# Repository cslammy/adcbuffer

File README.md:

# adcbuffer
Op amp buffer with clamp, to protect your MCU's ADC pins

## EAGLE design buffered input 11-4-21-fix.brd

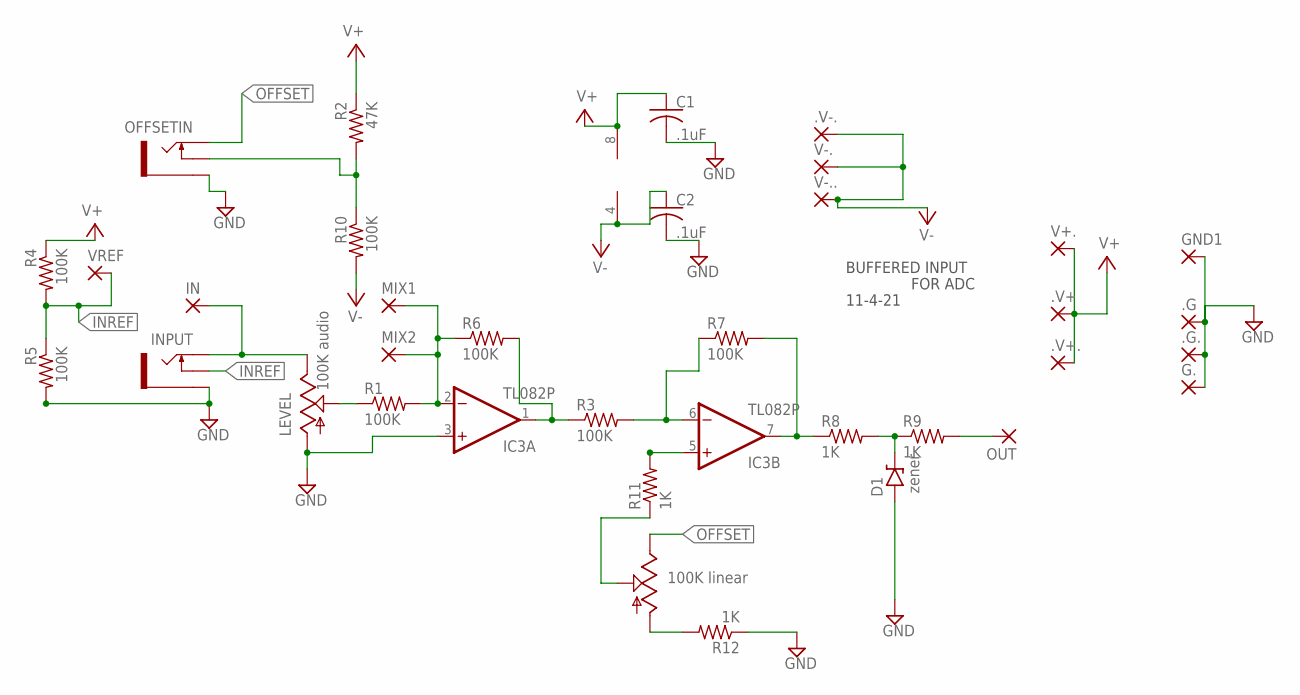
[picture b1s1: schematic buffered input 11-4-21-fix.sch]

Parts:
.G, .G., .V-.: 3,17/1,3
.V+, .V+.: 2,54/1,0
C1, C2: .1uF; C025-025X050
D1: zener; DO41-2
G.: 3,17/1,3
GND1: 3,17/1,3
IC3: TL082P; DIL08
IN: 3,17/1,3
INPUT: THONKICONNNEW; WQP-PJ301M-12_JACK
LEVEL: 100K audio; 9MM_SNAP-IN_POT
MIX1, MIX2: 3,17/1,3
OFFSET: 100K linear; 9MM_SNAP-IN_POT
OFFSETIN: THONKICONNNEW; WQP-PJ301M-12_JACK
OUT: 3,17/1,3
R1, R3, R4, R5, R6, R7, R10: 100K; 0204/7
R2: 47K; 0204/7
R8, R9, R11, R12: 1K; 0204/7
V+.: 2,54/1,0
V-., V-..: 3,17/1,3
VREF: 3,17/1,3

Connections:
CHARREF: OFFSETIN.P$2_SWITCH (SWITCH), R2.2, R10.1
GND: .G.1, .G..1, C1.2, C2.2, D1.A, G..1, GND1.1, IC3.3 (+IN), INPUT.P$3_SLEEVE (SLEEVE), LEVEL.1 (A), OFFSETIN.P$3_SLEEVE (SLEEVE), R5.2, R12.1
INREF: INPUT.P$2_SWITCH (SWITCH), R4.2, R5.1, VREF.1
unnamed: IN.1, INPUT.P$1_TIP (TIP), LEVEL.3 (E)
unnamed: OUT.1, R9.2
unnamed: OFFSET.1 (A), R12.2
unnamed: IC3.5 (+IN), R11.2
unnamed: IC3.6 (-IN), R3.2, R7.1
unnamed: IC3.1 (OUT), R3.1, R6.2
unnamed: IC3.2 (-IN), MIX1.1, MIX2.1, R1.2, R6.1
unnamed: LEVEL.2 (S), R1.1
unnamed: OFFSET.2 (S), R11.1
unnamed: IC3.7 (OUT), R7.2, R8.1
unnamed: D1.C, R8.2, R9.1
OFFSET: OFFSET.3 (E), OFFSETIN.P$1_TIP (TIP)
V+: .V+.1, .V+..1, C1.1, IC3.8 (V+), R2.1, R4.1, V+..1
V-: .V-..1, C2.1, IC3.4 (V-), R10.2, V-..1, V-...1

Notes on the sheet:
BUFFERED INPUT
11-4-21
FOR ADC

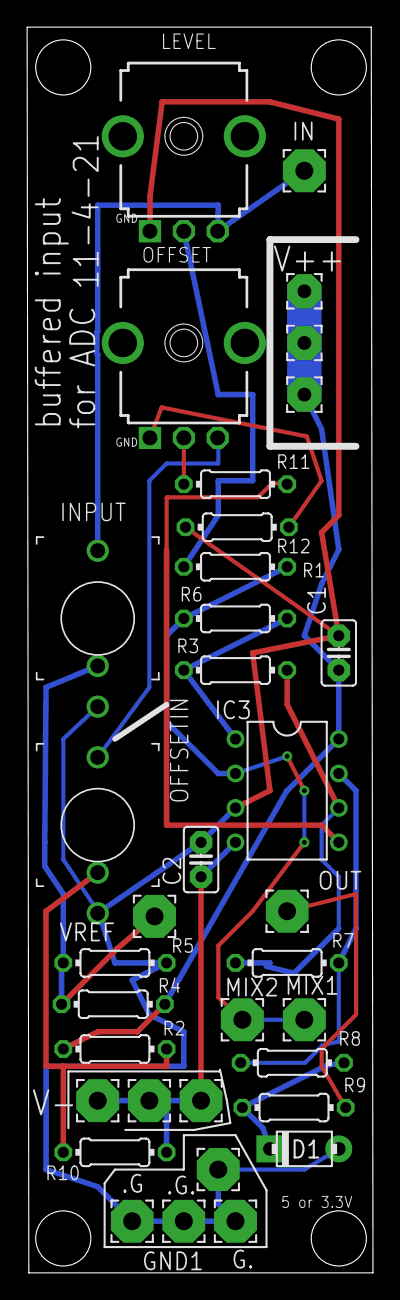
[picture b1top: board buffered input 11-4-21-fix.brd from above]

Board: 2 copper layers, 25.5 x 91.9 mm, 35 parts (0 on the bottom side), 17 nets.

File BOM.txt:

Part     Value       Device           Package            Description                                       DATA_SHEET                                                            
                                                                                                        
C1       .1uF        C-US025-025X050  C025-025X050       CAPACITOR, American symbol                                                                                              
C2       .1uF        C-US025-025X050  C025-025X050       CAPACITOR, American symbol                                                                                              
D1       zener       ZENER.2          DO41-2             5V zener diode                                                                                                                        
                                                                                                        
IC3      TL082P      TL082P           DIL08              OP AMP                                             Data sheet 
                                                                                                        
INPUT                THONKICONNNEW    WQP-PJ301M-12_JACK 3.5mm socket for Eurorack modular synths                                                                                
LEVEL    100K audio  9MM_SNAP-IN_POT_ 9MM_SNAP-IN_POT    9mm vertical snap-in pot, Alpha / Panasonic style                                                                       
                                                                                                      
OFFSET   100K linear 9MM_SNAP-IN_POT_ 9MM_SNAP-IN_POT    9mm vertical snap-in pot, Alpha / Panasonic style                                                                       
OFFSETIN             THONKICONNNEW    WQP-PJ301M-12_JACK 3.5mm socket for Eurorack modular synths                                                                                
                                                                                                        
R1       100K        R-US_0204/7      0204/7             RESISTOR, American symbol                                                                                               
R2       47K         R-US_0204/7      0204/7             RESISTOR, American symbol                                                                                               
R3       100K        R-US_0204/7      0204/7             RESISTOR, American symbol                                                                                               
R4       100K        R-US_0204/7      0204/7             RESISTOR, American symbol                                                                                               
R5       100K        R-US_0204/7      0204/7             RESISTOR, American symbol                                                                                               
R6       100K        R-US_0204/7      0204/7             RESISTOR, American symbol                                                                                               
R7       100K        R-US_0204/7      0204/7             RESISTOR, American symbol                                                                                               
R8       1K          R-US_0204/7      0204/7             RESISTOR, American symbol                                                                                               
R9       1K          R-US_0204/7      0204/7             RESISTOR, American symbol                                                                                               
R10      100K        R-US_0204/7      0204/7             RESISTOR, American symbol                                                                                               
R11      1K          R-US_0204/7      0204/7             RESISTOR, American symbol                                                                                               
R12      1K          R-US_0204/7      0204/7             RESISTOR, American symbol

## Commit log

2022-01-30 Initial upload--gerber, BOM, eagle files, PDFs
    Please see the blog post here for details about this project: https://audiodiwhy.blogspot.com/2022/01/bench-buffer-protect-your-ard-weeno.html
